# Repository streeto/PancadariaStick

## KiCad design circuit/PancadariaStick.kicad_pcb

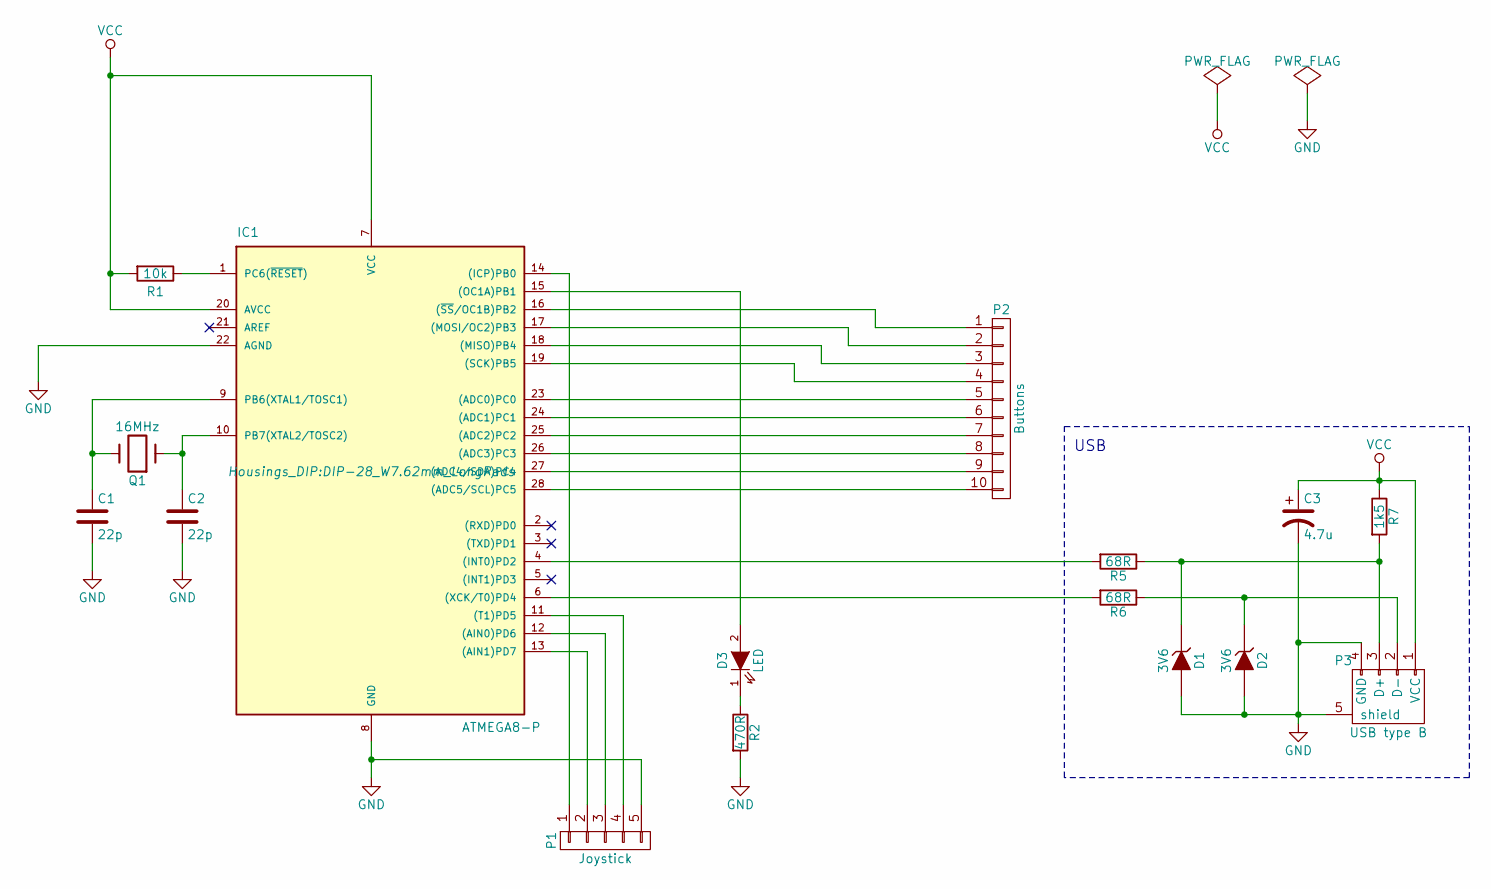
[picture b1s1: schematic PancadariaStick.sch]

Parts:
C1, C2: 22p; C_Rect_L7_W2_P5
C3: 4.7u; C_Radial_D5_L11_P2
D1, D2: 3V6; D3
D3: LED; LED-5MM
IC1: ATMEGA8-P; DIP-28_W7.62mm_LongPads
P1: Joystick; TerminalBlock_Pheonix_MKDS1.5-5pol
P2: Buttons; TerminalBlock_Pheonix_MKDS1.5-10pol
P3: USB type B; USB_B
Q1: 16MHz; Crystal_HC49-U_Vertical
R1: 10k; Resistor_Horizontal_RM7mm
R2: 470R; Resistor_Horizontal_RM7mm
R5, R6: 68R; Resistor_Horizontal_RM7mm
R7: 1k5; Resistor_Horizontal_RM7mm

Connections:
GND: C1.2, C2.2, C3.2, D1.2 (A), D2.2 (A), IC1.8 (GND), IC1.22 (AGND), P1.5, P3.4 (GND), P3.5 (shield), R2.2
unnamed: C1.1, IC1.9 (PB6(XTAL1/TOSC1)), Q1.2
unnamed: C2.1, IC1.10 (PB7(XTAL2/TOSC2)), Q1.1
unnamed: D1.1 (K), P3.3 (D+), R5.1, R7.2
unnamed: D2.1 (K), P3.2 (D-), R6.1
unnamed: D3.1 (K), R2.1
unnamed: D3.2 (A), IC1.15 ((OC1A)PB1)
unnamed: IC1.1 (PC6(~RESET~)), R1.1
unnamed: IC1.4 ((INT0)PD2), R5.2
unnamed: IC1.6 ((XCK/T0)PD4), R6.2
unnamed: IC1.11 ((T1)PD5), P1.4
unnamed: IC1.12 ((AIN0)PD6), P1.3
unnamed: IC1.13 ((AIN1)PD7), P1.2
unnamed: IC1.14 ((ICP)PB0), P1.1
unnamed: IC1.16 ((~SS~/OC1B)PB2), P2.1
unnamed: IC1.17 ((MOSI/OC2)PB3), P2.2
unnamed: IC1.18 ((MISO)PB4), P2.3
unnamed: IC1.19 ((SCK)PB5), P2.4
unnamed: IC1.23 ((ADC0)PC0), P2.5
unnamed: IC1.24 ((ADC1)PC1), P2.6
unnamed: IC1.25 ((ADC2)PC2), P2.7
unnamed: IC1.26 ((ADC3)PC3), P2.8
unnamed: IC1.27 ((ADC4/SDA)PC4), P2.9
unnamed: IC1.28 ((ADC5/SCL)PC5), P2.10
VCC: C3.1, IC1.7 (VCC), IC1.20 (AVCC), P3.1 (VCC), R1.2, R7.1

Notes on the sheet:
USB

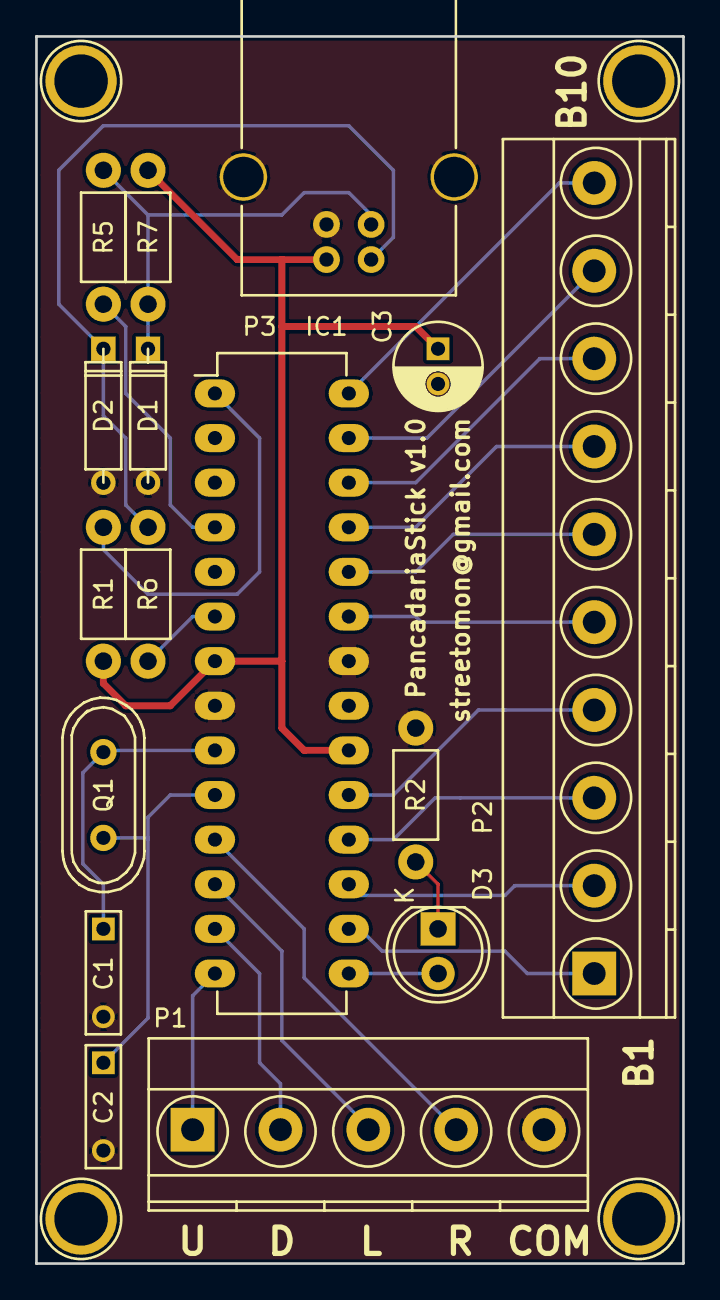
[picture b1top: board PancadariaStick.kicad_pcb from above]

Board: 2 copper layers, 36.8 x 69.9 mm, 16 parts (0 on the bottom side), 25 nets.

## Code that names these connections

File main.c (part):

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 * then the 4 diretions.
 *
 * The pins are mapped as follows:
 *     Pin      --- --- PB5 PB4 PB3 PB2 PB1 PB0
 *     Function             B04 B03 B02 B01   R
 *
 *     Pin      --- --- PC5 PC4 PC3 PC2 PC1 PC0
 *     Function         B10 B09 B08 B07 B06 B05
 *
 *     Pin      PD7 PD6 PD5 --- PD3 --- PD1 PD0
 *     Function   L   U   D
 */
const InputMap_t inputMap[NUM_INPUT] = { { MAP_PORTB, _BV(1) }, { MAP_PORTB, _BV(2) },
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
static inline void LED_on(void)
{
	PORTB &= ~(1 << PB5);
}

/* ------------------------------------------------------------------------- */

static inline void LED_off(void)
{
	PORTB |= (1 << PB5);
}

/* ------------------------------------------------------------------------- */

static inline void LED_toggle(void)
{
	if (~PORTB & (1 << PB5)) {
		LED_off();
	} else {
		LED_on();
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	InputMap_t map;
	uint8_t i;

	DDRB |= (1 << PB5); // Output: LED attached to PB5

	/* Inputs with pullup. */
	for(i = 0; i < NUM_INPUT; ++i) {
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
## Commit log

2016-08-11 Initial import.
2016-08-16 Fixed button mapping to match ATmega8 B and C port layout.
2016-08-16 Added circuit drawings.
2016-08-16 Updated ignored files.
2016-08-16 Fixed "jumper vias" drill size.
2016-08-26 Changed traces width to 0.8 mm.
2016-11-09 Updated board, removed ISP header, changed connectors to block terminals, added LED. Added plots.
2016-11-09 Updated USB ProductID, kindly provided by pid.codes <http://pid.codes/>.
2016-11-09 Minor changes in the schematic and pcb files, does not actually changes the layout.
2016-12-20 Major input refactor, added button mapping support.
2016-12-23 Small changes in EEPROM functions and mapping.
2017-01-06 Minor changes.
2017-01-06 Added an 8 ms delay before sending the USB report, for better multi-button input handling.
2017-01-10 Better timing code, avoid sending unneeded reports.

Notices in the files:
main.c:
Copyright: (C) 2016 By André Luiz de Amorim
Copyright: (C) 2008 By Objective Development Software Gmbh
License: GNU GPL v2 (see License.txt), GNU GPL v3 or proprietary (CommercialLicense.txt)
